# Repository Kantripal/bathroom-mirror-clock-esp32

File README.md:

# Badspiegel-Uhr auf ESP32 (Ersatz für „Mirror Timer 90003614“)

**English summary:** Drop-in replacement for the clock insert of a bathroom mirror cabinet. The original
module is labelled "Mirror Timer 90003614, 6 - 12 VDC 0.36W, produced by SNT for Wessel Licht für Möbel GmbH"
(PCB "XD-903 REV.03"). It lost the time after every power cut. This replacement uses a Seeed XIAO
ESP32-C3 with ESPHome, a DS3231 real-time clock with coin cell and a white TM1637 4-digit display. It gets
the time over Wi-Fi, keeps it without power, dims itself by sun position and can show the outdoor temperature
from Home Assistant. It fits the original rail and uses the original 12 V and push-button cables. Note:
the new housing is longer (141.9 mm instead of 96.8 mm) and deeper (27.9 mm instead of 17.5 mm) than the
original. It fits my mirrors (30 mm gap behind the slot), other mirrors are untested. The
repository contains the ESPHome configuration, a two-layer KiCad board (Gerber files with the Aisler logo
placeholder, usable at any manufacturer) and an OpenSCAD housing with ready-to-print STL and 3MF files. Documentation is in German.
Licence: CC BY-NC-SA 4.0 (no commercial use).

Stichworte: Badspiegel Uhr Ersatz, Spiegelschrank Uhr geht nach, Spiegeluhr verliert Zeit, Uhrmodul
Badspiegel, Wessel Licht, XD-903, XD-904, XiongDa, mirror clock module, bathroom mirror clock replacement,
ESPHome, Home Assistant.

> Dieses Projekt ist nicht mit Wessel Licht für Möbel GmbH oder dem Hersteller des Spiegels verbunden.
> Die Namen stehen hier nur, damit man das passende Original erkennt.

## Worum es geht

Im Spiegelschrank steckt hinter einer milchigen Scheibe eine kleine Uhr in einer Schiene. Die Uhr bekommt
nur Strom, wenn das Licht am Spiegel an ist. Eine Knopfzelle soll die Zeit halten, wenn das Licht aus ist.
Bei diesem Modul klappt das nicht: Die Uhr geht falsch, auch mit neuer Knopfzelle. Stellen kann man sie nur
mühsam mit einem kleinen Knopf unter dem Spiegel.

Die neue Uhr passt in dieselbe Schiene und stellt sich selbst. Sie ist aber länger und tiefer als das
Original (Abschnitt „Das Gehäuse“).

## So erkennst du das Original

- Schild auf der Rückseite: „90003614 / Mirror Timer 6 - 12 VDC 0.36W 4000 K, LED-Mini-Anschluss“.
- Aufdruck auf der Platine: „XD-903 REV.03 2015.07.15“. Händler nennen als Hersteller XiongDa. Ein
  ähnliches Modul heißt XD-904. Ob es in dieselbe Schiene passt, habe ich nicht geprüft.
- Gelbe Ziffern, Knopfzelle CR2032.
- Gehäuse außen 96,8 × 27,0 × 17,5 mm, mit zwei Flügeln für die Schiene.
- Zwei Kabelpaare: Strom (12 V) und ein Knopf (kleiner Joystick unter dem Spiegel).

## Was die neue Uhr kann

- **Sie stellt sich selbst.** Sie holt die genaue Zeit über das WLAN aus dem Internet.
- **Sie vergisst die Zeit nicht.** Ein Uhrmodul mit Knopfzelle zählt weiter, wenn das Licht aus ist.
- **Sie ist sofort da.** Nach dem Einschalten des Lichts steht die Uhrzeit nach 1 bis 3 Sekunden. Sie
  kommt direkt aus dem Uhrmodul und wartet nicht auf das WLAN.
- **Sie braucht wenig Strom.** Etwa 0,13 W statt 0,36 W beim Original, also rund ein Drittel.
- **Sie dimmt sich selbst.** Sie rechnet aus, ob die Sonne schon untergegangen ist, und leuchtet nachts
  schwächer. Dafür braucht sie keine weitere Technik.
- **Morgen-Briefing (nur mit Home Assistant):** Morgens zeigt sie abwechselnd die Uhrzeit, die
  Außentemperatur, die Höchsttemperatur des Tages und die Regenmenge.
- **Der Knopf unter dem Spiegel:** kurz drücken zeigt die Werte einmal. Lang drücken (1 bis 5 Sekunden)
  schaltet das Morgen-Briefing an oder aus.

Home Assistant ist eine Software für das eigene Zuhause. Ohne Home Assistant läuft die Uhr auch, dann
nur ohne Morgen-Briefing.

## Sicherheit

> **WARNUNG:** Hinter dem Spiegel liegt ein Netzteil an 230 V. Öffne das Netzteil nicht. Arbeite nur an
> den Kabeln im Einschubschacht der Uhr. Dort liegen nur 12 V. Wenn du an das Netzteil musst, schalte
> vorher die Sicherung aus und prüfe, dass keine Spannung mehr anliegt. Sonst kann ein Stromschlag dich töten.

Die neue Uhr braucht etwa 0,011 A bei 12 V, also etwa 0,13 W. Das ist weniger als das Original (0,36 W).

## Was du brauchst

Fertige Module mit Stiftleisten. Es gibt keine winzigen Bauteile zum Löten.

| Ref. | Teil | Wozu |
|---|---|---|
| U1 | Seeed XIAO ESP32-C3 mit Antenne | kleiner Rechner mit WLAN, das Gehirn der Uhr |
| U2 | Uhrmodul DS3231 (ZS-042) mit Knopfzelle CR2032 | zählt die Zeit weiter, wenn das Licht aus ist |
| U3 | Spannungswandler MP1584 | macht aus 12 V die 5 V für die Module |
| U4 | Pegelwandler, 4 Kanäle (BSS138) | übersetzt zwischen 3,3 V am XIAO und 5 V an der Anzeige |
| U5 | Anzeige TM1637, 4 Ziffern | die Ziffern. Weiß ist hier verbaut, andere Farben passen auch (siehe unten) |
| D1, D2 | Diode 1N5819 | D1: XIAO darf gleichzeitig an USB und an 12 V. D2: Schutz, falls Plus und Minus vertauscht sind |
| R1, R2 | Widerstand 2,2 kΩ | für die Leitungen zum Uhrmodul |
| R3, R4 | Widerstand 10 kΩ und 1 kΩ | Schutz am Eingang für den Knopf |
| C1 | Elko 47 µF 25 V | glättet den Strom vom Netzteil im Spiegel |
| C2 | Kondensator 100 nF 50 V | entstört den Eingang für den Knopf |
| TP1 | Buchsenleiste 4-polig | Messpunkte 12V, 5V, 3V3, GND |
| J1, J2 | Kabelstücke vom Original | Strom und Knopf, mit den alten Steckern |

**Andere Farbe der Anzeige:** Das Anzeigemodul gibt es in mehreren Farben, zum Beispiel in Blau. Eine
andere Farbe passt, wenn das Modul gleich groß ist und die Stifte an denselben Stellen sitzen. Prüfe das mit den Maßen in
`bauteile/tm1637-anzeige/Steckbrief.md`.

Für jedes Modul gibt es in `bauteile/` einen Steckbrief mit den Maßen und der Belegung der Stifte.

## Einstellungen, die bei mir angenehm sind

Die Helligkeit geht von Stufe 0 (dunkelste, nicht aus) bis Stufe 7 (hellste). Bei mir ist sie fest auf
**Stufe 3 am Tag** und **Stufe 2 in der Nacht** eingestellt. Hinter der milchigen Scheibe ist das gut
lesbar und blendet nachts nicht. Das sind meine Werte, du kannst andere nehmen. Du findest sie in
`badspiegel-uhr.yaml` im Abschnitt `helligkeit_setzen`.

Das Morgen-Briefing läuft ab Werk von 6 bis 10 Uhr. Du kannst das Zeitfenster in Home Assistant ändern.

## Die Platine

Die Platine ist die grüne Leiterplatte, auf die alle Module gesteckt und gelötet werden. Statt Drähten
verbinden Leiterbahnen die Teile. Man lässt sie bei einem Platinenhersteller fertigen. Dafür lädt man dort
eine ZIP-Datei mit den Fertigungsdateien hoch. Die Platine ist 134,1 × 27 mm groß. Sie hat Leiterbahnen auf
beiden Seiten. Das ist bei jedem Hersteller der Standard.

Die Fertigungsdateien liegen in `Platine/fertigung.zip`. Sie passen für jeden Hersteller.

Auf der Rückseite ist ein leeres Rechteck aus sehr dünnen Linien. Bei Aisler (Deutschland) ist das ein
Platzhalter: Aisler druckt dort sein Logo auf und gibt dafür einen Rabatt. Andere Hersteller drucken den
Rahmen dünn oder gar nicht, manche fragen kurz nach. Antworte dann: „Der Rahmen kann entfallen.“ Im
Gehäuse sieht man ihn nicht, und er ist nur Aufdruck, keine Leiterbahn.

**Empfehlungscode für Aisler:** Mit dem Code `MakeInEurope-TNGXI` bekommst du 10 Euro Rabatt auf deine
erste Bestellung bei Aisler. **Hinweis:** Das ist mein persönlicher Empfehlungscode. Wenn du ihn benutzt,
bekomme ich 10 Euro Guthaben bei Aisler. Du zahlst dadurch nichts mehr, du sparst die 10 Euro.

Meine Platinen kamen von Aisler (Oberfläche ENIG, 1,6 mm dick, 3 Stück). Das KiCad-Projekt liegt ebenfalls
in `Platine/`, falls du etwas ändern willst.

## Zusammenbauen

Löte zuerst die flachen Teile, dann die hohen. Die Anzeige kommt zuletzt, weil sie die Rückseite verdeckt.

1. Feile die kleinen Reste an den Kanten der Platine ab, bis die Kante glatt ist.
2. Löte D1 und D2 ein. Der Ring auf der Diode zeigt zum Lötpunkt „K“.
3. Löte R1 bis R4, C2 und TP1 ein.
4. Löte den Spannungswandler U3 ein. Lege 12 V an TP1 „12V“ und „GND“ an.
   Begrenze den Strom am Labornetzteil auf 0,1 A.
5. Miss an TP1 „5V“ gegen „GND“. Drehe an der kleinen Schraube des Wandlers, bis du 5,00 V misst.
   Schalte die 12 V wieder aus.
6. Löte C1 ein. Das lange Bein kommt in das eckige Loch „+“.
7. Löte den XIAO ein. Das eckige Loch ist D0.
8. Löte den Pegelwandler ein. Die Seite mit der Schrift zeigt nach oben, „5V“ liegt neben R1.
9. Löte das Uhrmodul ein. Lege es dabei auf den gedruckten Klotz (`Gehaeuse/druck/klotz.stl`).
10. Löte die Kabel an J1 (+12V, GND) und J2 (JOY, GND). Halte jedes Kabel mit einem Kabelbinder durch sein
    Loch in der Platine.
11. Kürze alle Drahtenden unter der Anzeige direkt an der Lötstelle. Dort sind nur etwa 3 mm Platz.
12. Löte die Anzeige von der Rückseite ein. Die Ziffern zeigen zur Kante mit TP1.
    Verdreht bekommt die Anzeige 5 V auf eine Datenleitung und geht kaputt.
13. Prüfe vor dem ersten Einschalten mit dem Messgerät: Zwischen 12V, 5V, 3V3 und GND an TP1 darf kein
    Kurzschluss sein.

Belegung am XIAO (aus `badspiegel-uhr.yaml`):

| Anschluss am Chip | Stift am XIAO | geht zu |
|---|---|---|
| GPIO4 | D2 | SDA am Uhrmodul |
| GPIO5 | D3 | SCL am Uhrmodul |
| GPIO6 | D4 | Pegelwandler L1, weiter zu CLK an der Anzeige |
| GPIO7 | D5 | Pegelwandler L2, weiter zu DIO an der Anzeige |
| GPIO10 | D10 | Knopf, gegen GND |

## Das Gehäuse

Das Gehäuse ist ein 3D-Druck. Es hat vier Teile: `gehaeuse`, `deckel`, `klotz` und `probe`. Die Flügel und
die Lage der Ziffern sind wie beim Original.

**Fertige Druckdateien** liegen in `Gehaeuse/druck/`, jedes Teil als STL und als 3MF. Lade sie direkt in
deinen Slicer (zum Beispiel PrusaSlicer oder OrcaSlicer). Die Teile liegen schon richtig herum für den Druck.

Wenn du Maße ändern willst, öffne `Gehaeuse/gehaeuse.scad` mit dem kostenlosen Programm OpenSCAD.

> **Hinweis:** Das neue Gehäuse ist länger als das Original: 141,9 mm statt 96,8 mm. Es ragt beim
> Einschieben etwa 45 mm weiter in den Spiegel hinein. Es ist auch tiefer: 27,9 mm statt 17,5 mm.
> In meinen Spiegeln ist hinter dem Einschubschacht ein Spalt von 30 mm und Platz für etwa 23 cm Länge.
> Dort passt es. Ob es in andere Spiegel passt, weiß ich nicht. Miss deshalb vorher nach, wie viel Platz
> hinter dem Schacht in der Länge und in der Tiefe frei ist.

1. Drucke zuerst `klotz` und `probe`. Mit der Probe prüfst du, ob das Gehäuse in deine Schiene passt.
2. Drucke `gehaeuse` und `deckel` aus ABS. Ich habe auf einer Prusa MK3S gedruckt.
3. Lege die Platine von hinten ein und schiebe sie bis zum Anschlag.
4. Lege die Antenne in die vier Ecken am Deckel. Führe das Antennenkabel seitlich an den zwei kleinen
   Knöpfen des XIAO vorbei. Sonst drückt der Deckel auf einen Knopf, und die Uhr bleibt dunkel.
5. Drücke den Deckel auf, bis alle fünf Haken einrasten.

Die Knopfzelle wechselst du durch das Fenster im Deckel. Der Deckel bleibt dabei zu.

Miss deine Schiene vor dem Druck nach. Die Maße stimmen für meine Spiegel. Für einen anderen Spiegel
änderst du die Werte am Anfang von `gehaeuse.scad`. Das Programm meldet dann, wenn ein Teil nicht passt.
Danach exportierst du die Teile neu, zum Beispiel so:

```bash
openscad -D 'teil="gehaeuse"' -o gehaeuse.stl gehaeuse.scad
```

## Programm aufspielen

Das Programm für den XIAO entsteht mit ESPHome. ESPHome ist ein kostenloses Werkzeug, das aus einer
Textdatei das fertige Programm baut.

1. Installiere ESPHome (getestet mit Version 2026.10.0).
2. Kopiere `secrets.yaml.example` nach `secrets.yaml`. Trage dort dein WLAN und die Schlüssel ein.
3. Trage in `badspiegel-uhr.yaml` unter `sun:` deinen Ort ein. Zwei Stellen nach dem Komma reichen.
4. Empfohlen: Wenn dein Router ein Zeitserver ist (zum Beispiel eine Fritzbox), trage ihn unter
   `platform: sntp` ein. Dann braucht die Uhr keinen Zugang zum Internet:

   ```yaml
   - platform: sntp
     servers:
       - 192.168.178.1   # Adresse deines Routers
   ```

   Ohne diesen Eintrag holt die Uhr die Zeit von öffentlichen Zeitservern im Internet.
5. Für das Morgen-Briefing: Trage unter `platform: homeassistant` die Namen deiner Sensoren ein.
6. Schließe den XIAO mit einem USB-C-Kabel an den Rechner an. Das Kabel muss Daten übertragen können,
   nicht nur Strom. Führe dann aus:

```bash
esphome run badspiegel-uhr.yaml
```

Danach geht das Aufspielen auch über WLAN. Die Uhr ist aber nur erreichbar, wenn das Licht am Spiegel an ist.

## Dateien

| Pfad | Inhalt |
|---|---|
| `badspiegel-uhr.yaml` | das Programm für ESPHome |
| `secrets.yaml.example` | Vorlage für WLAN und Schlüssel |
| `briefing.h`, `briefing_test.cpp` | Rechenteil des Morgen-Briefings und ein Test dafür |
| `Platine/` | Platine: KiCad-Projekt und die zwei ZIP-Dateien für die Fertigung |
| `Gehaeuse/druck/` | fertige Druckdateien (STL und 3MF) |
| `Gehaeuse/gehaeuse.scad` | Gehäuse zum Ändern in OpenSCAD |
| `Anzeigetest/` | Test der Anzeige an einem Arduino, ohne Löten |
| `bauteile/` | Steckbriefe der Module: Maße, Belegung, Messwerte |
| `bilder/` | Fotos |

## Lizenz

[CC BY-NC-SA 4.0](https://creativecommons.org/licenses/by-nc-sa/4.0/deed.de). Du darfst die Uhr nachbauen,
ändern und weitergeben. Nenne dabei dieses Projekt als Quelle. Gib Änderungen unter derselben Lizenz weiter.
Verkaufen und jede andere gewerbliche Nutzung sind nicht erlaubt. Der vollständige Text steht in `LICENSE`.

Datenblätter der Bauteile sind nicht Teil dieses Projekts. Sie gehören ihren Herstellern.

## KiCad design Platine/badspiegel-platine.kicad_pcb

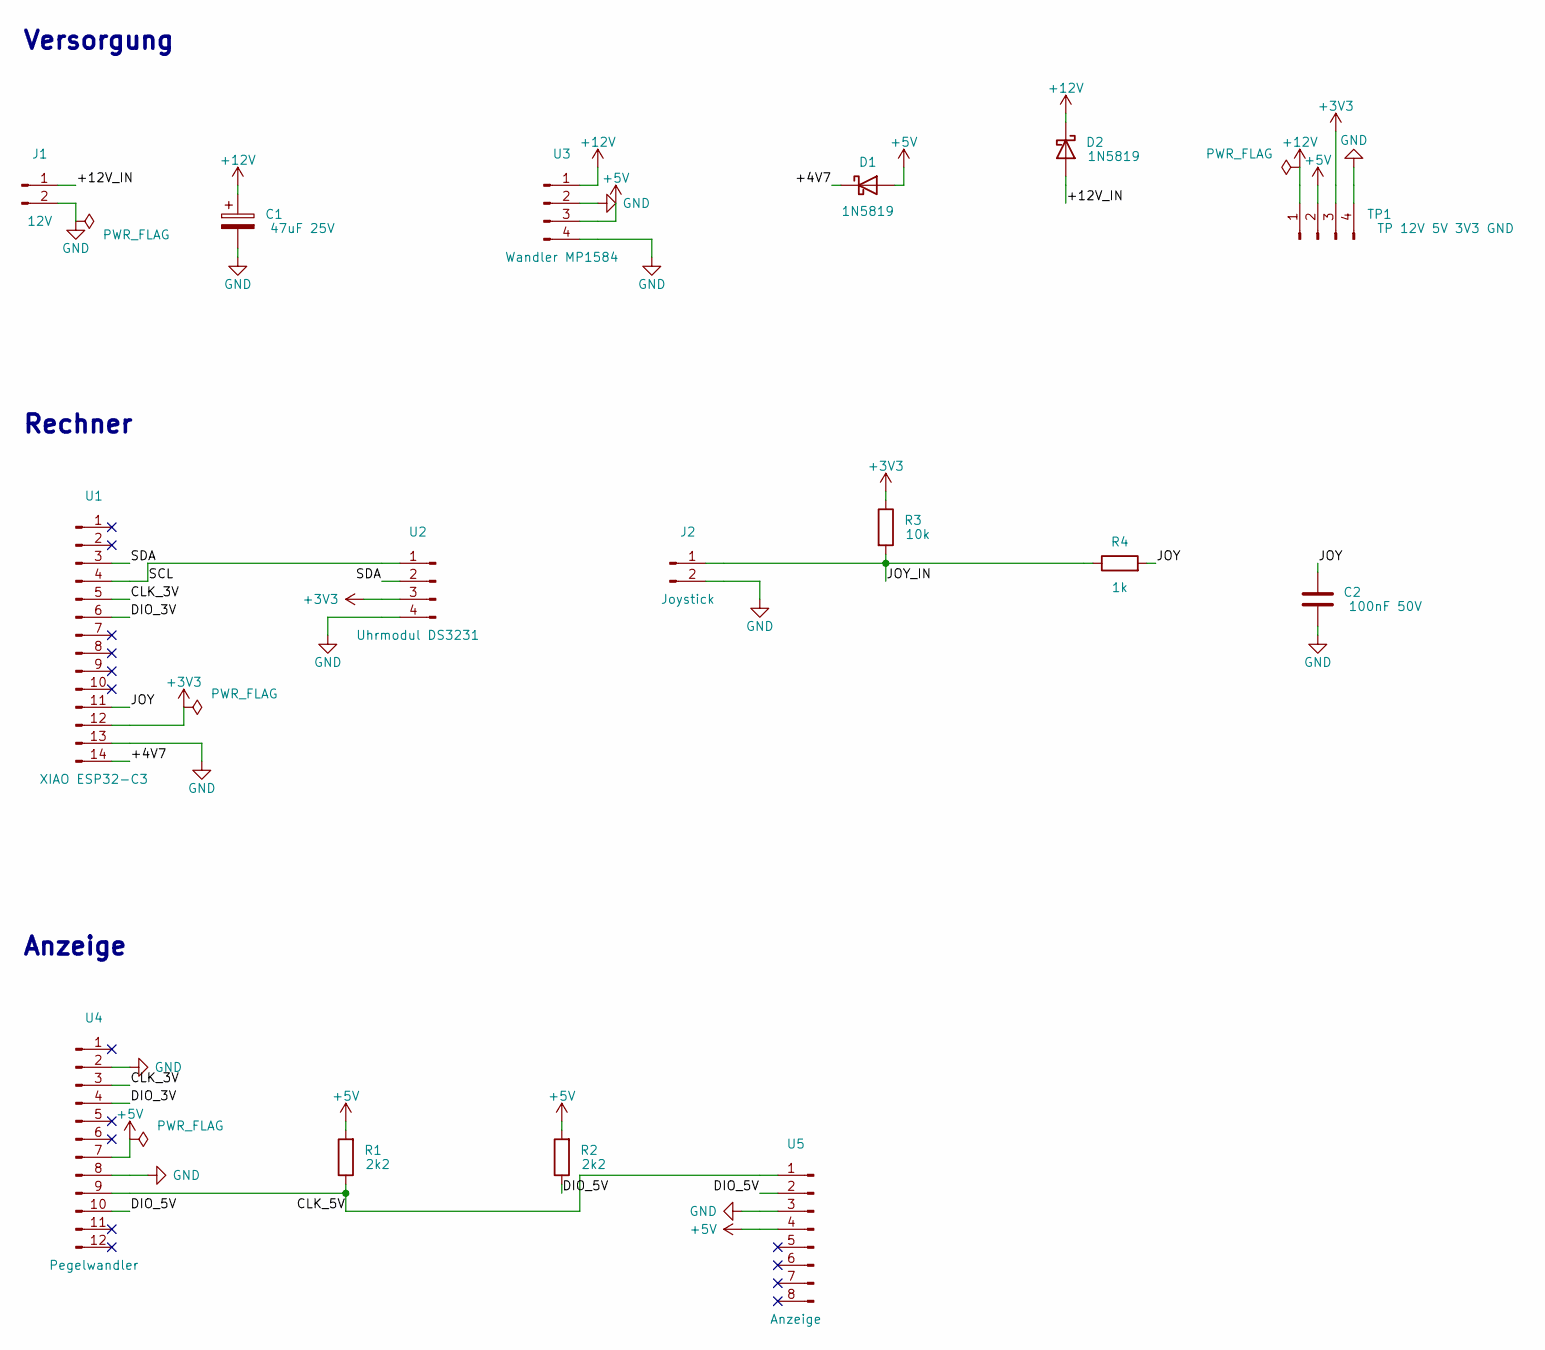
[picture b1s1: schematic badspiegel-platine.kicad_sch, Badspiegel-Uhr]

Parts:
C1: 47uF 25V; CP_Radial_D5.0mm_P2.00mm
C2: 100nF 50V; C_Disc_D5.0mm_W2.5mm_P5.00mm
D1, D2: 1N5819; D_DO-41_SOD81_P7.62mm_Horizontal
J1: 12V; Kabel_12V
J2: Joystick; Kabel_Joystick
R1, R2: 2k2; R_Axial_DIN0207_L6.3mm_D2.5mm_P7.62mm_Horizontal
R3: 10k; R_Axial_DIN0207_L6.3mm_D2.5mm_P7.62mm_Horizontal
R4: 1k; R_Axial_DIN0207_L6.3mm_D2.5mm_P7.62mm_Horizontal
TP1: TP 12V 5V 3V3 GND; Testpunkte_4er
U1: XIAO ESP32-C3; XIAO_C3_Sockel
U2: Uhrmodul DS3231; DS3231_ZS042_Sockel
U3: Wandler MP1584; MP1584_Sockel
U4: Pegelwandler; Pegelwandler_Sockel
U5: Anzeige; Anzeige_TM1637_Stifte

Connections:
+3V3: R3.1, TP1.3, U1.12, U2.3
+5V: D1.2 (A), R1.2, R2.2, TP1.2, U3.3, U4.7, U5.4
+12V: C1.1, D2.1 (K), TP1.1, U3.1
/+4V7: D1.1 (K), U1.14
/+12V_IN: D2.2 (A), J1.1
/CLK_3V: U1.5, U4.3
/CLK_5V: R1.1, U4.9, U5.1
/DIO_3V: U1.6, U4.4
/DIO_5V: R2.1, U4.10, U5.2
/JOY: C2.1, R4.2, U1.11
/JOY_IN: J2.1, R3.2, R4.1
/SCL: U1.4, U2.1
/SDA: U1.3, U2.2
GND: C1.2, C2.2, J1.2, J2.2, TP1.4, U1.13, U2.4, U3.2, U3.4, U4.2, U4.8, U5.3

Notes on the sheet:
Versorgung
Rechner
Anzeige

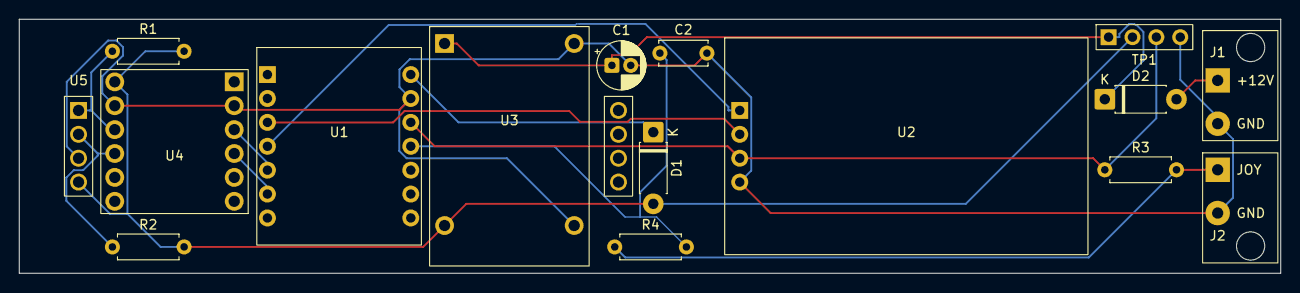
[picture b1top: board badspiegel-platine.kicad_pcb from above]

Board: 2 copper layers, 134.1 x 27.0 mm, 16 parts (0 on the bottom side), 14 nets.
